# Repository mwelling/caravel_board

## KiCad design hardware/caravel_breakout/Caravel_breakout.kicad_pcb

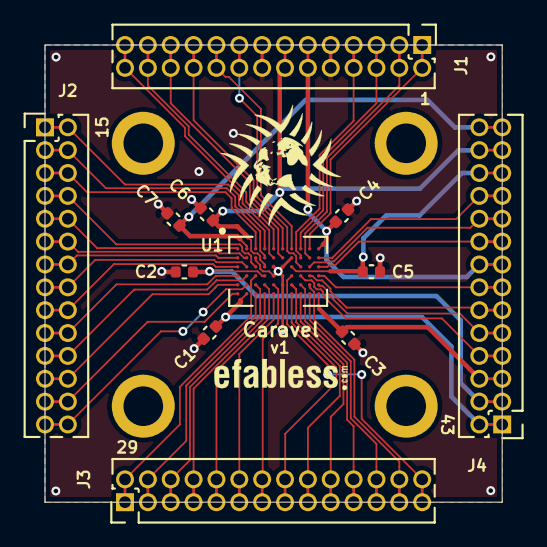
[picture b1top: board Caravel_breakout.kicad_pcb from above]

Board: 2 copper layers, 25.4 x 25.4 mm, 18 parts (0 on the bottom side), 53 nets.

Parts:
C1, C2, C3, C4, C5, C6, C7: 0.1uf; C_0402_1005Metric
H1, H2, H3, H4: Positioning Holes; MountingHole_2.2mm_M2_ISO7380_Pad
J1, J2, J3, J4: Conn_01x14_Female; PinHeader_2x14_P1.27mm_Vertical
T1: Logo; logo
T2: Logo; ef_logo
U1: Caravel; Caravel_WCSP

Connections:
Caravel_CSB: J4.17, J4.18, U1.C10
Caravel_D0: J4.13, J4.14, U1.D10
Caravel_D1: J4.11, J4.12, U1.D9
Caravel_SCK: J4.7, J4.8, U1.D8
GND: C1.1, C2.2, C3.2, C4.1, C5.1, C6.1, C7.1, J1.9, J1.10, J1.15, J1.16, U1.B3, U1.B7, U1.C5, U1.C6, U1.D5, U1.D6, U1.E6, U1.F6
gpio: J4.9, J4.10, U1.E10
mprj_io[0]: J3.27, J3.28, U1.D7
mprj_io[1]_SDO: J3.25, J3.26, U1.E9
mprj_io[2]_SDI: J3.23, J3.24, U1.F9
mprj_io[3]_CSB: J3.21, J3.22, U1.E8
mprj_io[4]_SCK: J3.19, J3.20, U1.F8
mprj_io[5]_ser_rx: J3.17, J3.18, U1.E7
mprj_io[6]_ser_tx: J3.15, J3.16, U1.F7
mprj_io[7]: J3.13, J3.14, U1.E5
mprj_io[8]: J3.11, J3.12, U1.F5
mprj_io[9]: J3.9, J3.10, U1.E4
mprj_io[10]: J3.7, J3.8, U1.F4
mprj_io[11]: J3.5, J3.6, U1.E3
mprj_io[12]: J3.3, J3.4, U1.F3
mprj_io[13]: J3.1, J3.2, U1.D3
mprj_io[14]: J2.27, J2.28, U1.E2
mprj_io[15]: J2.25, J2.26, U1.F1
mprj_io[16]: J2.23, J2.24, U1.E1
mprj_io[17]: J2.21, J2.22, U1.D2
mprj_io[18]: J2.19, J2.20, U1.D1
mprj_io[19]: J2.17, J2.18, U1.C1
mprj_io[20]: J2.15, J2.16, U1.C2
mprj_io[21]: J2.13, J2.14, U1.B1
mprj_io[22]: J2.11, J2.12, U1.B2
mprj_io[23]: J2.9, J2.10, U1.A1
mprj_io[24]: J2.7, J2.8, U1.C3
mprj_io[25]: J2.5, J2.6, U1.A3
mprj_io[26]: J2.3, J2.4, U1.B4
mprj_io[27]: J2.1, J2.2, U1.A4
mprj_io[28]: J1.27, J1.28, U1.B5
mprj_io[29]: J1.25, J1.26, U1.A5
mprj_io[30]: J1.23, J1.24, U1.B6
mprj_io[31]: J1.21, J1.22, U1.A6
mprj_io[32]: J1.19, J1.20, U1.A7
mprj_io[33]: J1.17, J1.18, U1.C8
mprj_io[34]: J1.7, J1.8, U1.B8
mprj_io[35]: J1.5, J1.6, U1.A8
mprj_io[36]: J1.3, J1.4, U1.B9
mprj_io[37]: J1.1, J1.2, U1.A9
vccd: C4.2, J1.11, J1.12, J4.15, J4.16, U1.A10
vccd1: C1.2, J4.1, J4.2, U1.F2
vccd2: C7.2, J4.27, J4.28, U1.A2
vdda: C3.1, J4.5, J4.6, U1.F10
vdda1: C2.1, J4.3, J4.4, U1.D4
vdda2: C5.2, J4.23, J4.24, U1.C7
vddio: C6.2, J1.13, J1.14, J4.25, J4.26, U1.C4
xclk: J4.19, J4.20, U1.C9
~RST: J4.21, J4.22, U1.B10

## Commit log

2021-10-22 Update caravel breakout PCB
    Switches to smaller passives.
    Moves passives closer to the IC pads.
    Increases the width of the power traces.
    Decreases the clearance on the PCB pours.
    Tweaks the silkscreen as needed.
